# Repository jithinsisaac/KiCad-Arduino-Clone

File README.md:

# Arduino Clone with RTC & Extended EEPROM
Herewith lies the KiCad files for an Arduino Clone with RTC & Extended EEPROM

This project is part of the coursework of the KiCad course on Udemy taught by Dr. Peter Dalmaris

[Udemy Course Link](https://www.udemy.com/course/kicad-like-a-pro-2e/)

## Components used

1. ATMega328P
1. DS1337 RTC
1. 24LC1025 EEPROM

**3D View of PCB-Front**

**3D View of PCB-Back**

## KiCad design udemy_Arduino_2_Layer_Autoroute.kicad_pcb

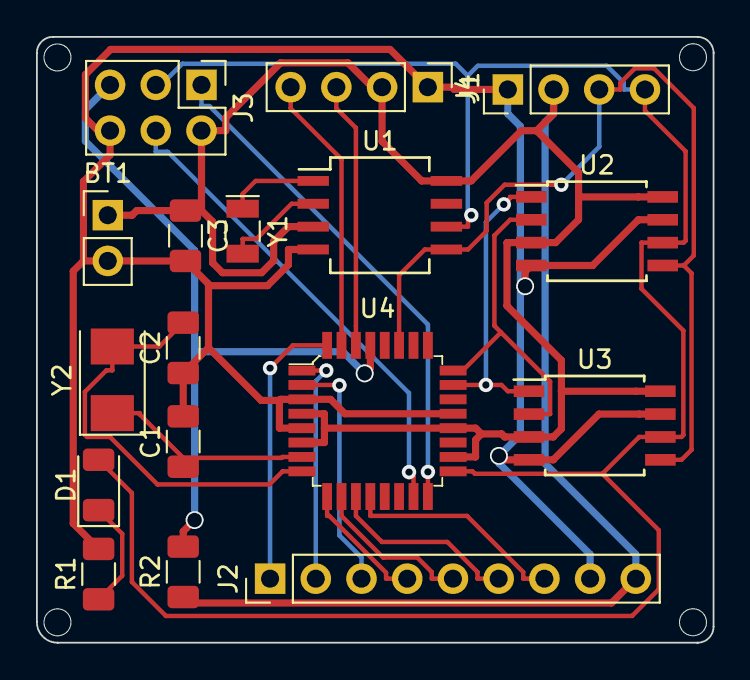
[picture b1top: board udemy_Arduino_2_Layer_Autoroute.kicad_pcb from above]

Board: 2 copper layers, 37.6 x 33.7 mm, 17 parts (0 on the bottom side), 23 nets.

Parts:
BT1: Battery3V3; PinHeader_1x02_P2.54mm_Vertical
C1, C2: 22pF; C_1206_3216Metric
C3: 10uF; C_1206_3216Metric
D1: LED; LED_1206_3216Metric
J1: Serial; PinHeader_1x04_P2.54mm_Vertical
J2: Digital Pins; PinHeader_1x09_P2.54mm_Vertical
J3: ICSP; PinHeader_2x03_P2.54mm_Vertical
J4: I2C; PinHeader_1x04_P2.54mm_Vertical
R1: 330Ohm; R_1206_3216Metric
R2: 10kOhm; R_1206_3216Metric
U1: DS1337_RTC_I2C_IJS_V1; SO-8_5.3x6.2mm_P1.27mm
U2, U3: 24LC1025; SOIJ-8_5.3x5.3mm_P1.27mm
U4: ATMEGA328P-AU; TQFP-32_7x7mm
Y1: Crystal 32MHz; Crystal_SMD_MicroCrystal_CC7V-T1A-2Pin_3.2x1.5mm
Y2: Crystal 16MHz; Crystal_SMD_5032-2Pin_5.0x3.2mm

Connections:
/ADDS1: U2.1, U3.1, U4.23
/ADDS2: U2.2, U3.2, U4.24
/D2: J2.1, U4.32
/D3: J2.2, U4.1
/D4: J2.3, U4.2
/D5: J2.4, U4.9
/D6: J2.5, U4.10
/D7: J2.6, U4.11
/D8: J2.7, U4.12
/MISO: J3.1, U4.16
/MOSI: J3.4, U4.15
/RESET: J3.5, R2.2, U4.29
/RX: J1.3, U4.30
/SCK: D1.2, J3.3, J4.4, U1.6, U2.6, U3.6, U4.17
/SDA: J4.3, U1.5, U2.5, U3.5, U4.27
/TX: J1.4, U4.31
/VCC: BT1.1, C3.1, J1.2, J2.9, J3.2, J4.2, R2.1, U1.3, U1.8, U2.3, U2.8, U3.3, U3.8, U4.4, U4.6, U4.18, U4.20
GNDPWR: BT1.2, C1.2, C2.1, C3.2, J1.1, J2.8, J3.6, J4.1, R1.2, U1.4, U2.4, U2.7, U3.4, U3.7, U4.3, U4.5, U4.21
unnamed: C1.1, U4.7, Y2.1
unnamed: C2.2, U4.8, Y2.2
unnamed: D1.1, R1.1
unnamed: U1.1, Y1.1
unnamed: U1.2, Y1.2
